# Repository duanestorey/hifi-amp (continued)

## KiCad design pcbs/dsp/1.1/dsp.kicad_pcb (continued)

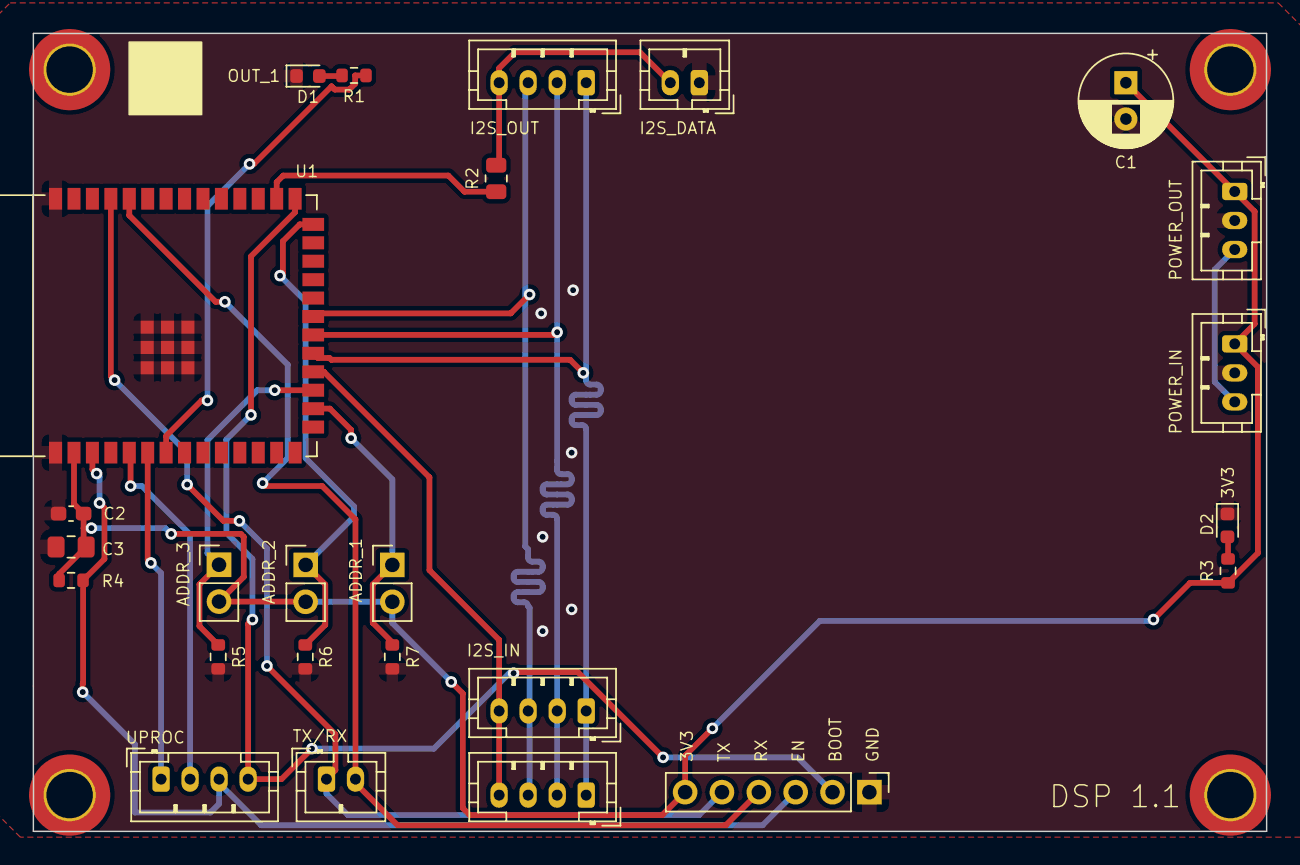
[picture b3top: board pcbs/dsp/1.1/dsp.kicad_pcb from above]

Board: 2 copper layers, 85.0 x 55.0 mm, 29 parts (0 on the bottom side), 21 nets.

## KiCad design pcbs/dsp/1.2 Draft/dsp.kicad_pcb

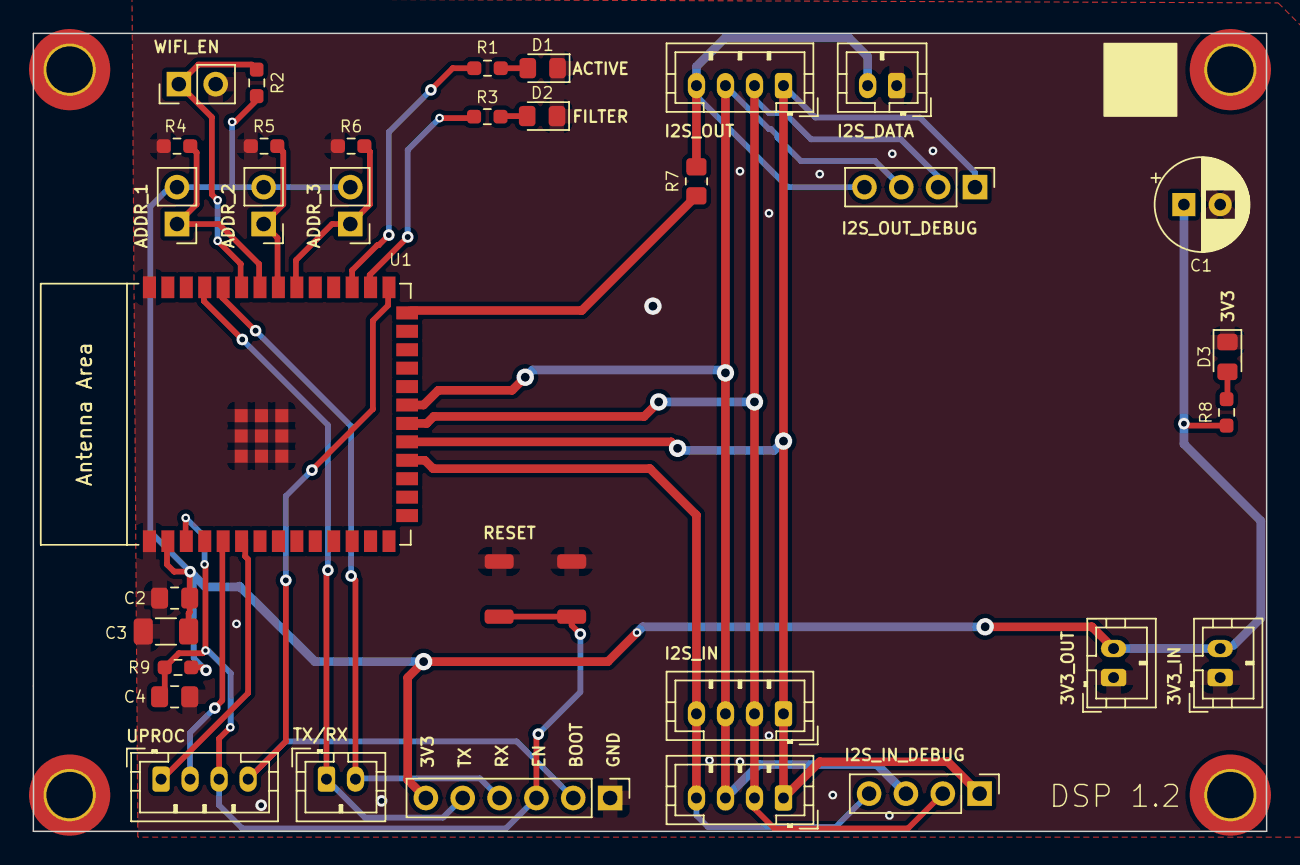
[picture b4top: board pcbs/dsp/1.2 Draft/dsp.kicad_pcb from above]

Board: 2 copper layers, 85.0 x 55.0 mm, 37 parts (0 on the bottom side), 23 nets.

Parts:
C1: 220u 16V; CP_Radial_D6.3mm_P2.50mm
C2, C4: 0.1u; C_0805_2012Metric_Pad1.18x1.45mm_HandSolder
C3: 10u; C_1206_3216Metric_Pad1.33x1.80mm_HandSolder
D1: RED; D_0805_2012Metric_Pad1.15x1.40mm_HandSolder
D2, D3: BLUE; D_0805_2012Metric_Pad1.15x1.40mm_HandSolder
H1, H2, H3, H4: MountingHole; MountingHole_3.2mm_M3_DIN965_Pad_TopOnly
J1, J5, J6, J7: Conn_01x02_Pin; PinHeader_1x02_P2.54mm_Vertical
J2, J10, J11, J15: Conn_01x04_Pin; JST_PH_B4B-PH-K_1x04_P2.00mm_Vertical
J3, J8, J9, J12: Conn_01x02_Pin; JST_PH_B2B-PH-K_1x02_P2.00mm_Vertical
J4, J13: Conn_01x04_Pin; PinHeader_1x04_P2.54mm_Vertical
J14: Conn_01x06_Pin; PinHeader_1x06_P2.54mm_Vertical
R1, R3, R8: 150R; R_0603_1608Metric_Pad0.98x0.95mm_HandSolder
R2, R4, R5, R6, R9: 4.7K; R_0603_1608Metric_Pad0.98x0.95mm_HandSolder
R7: 22R; R_0805_2012Metric_Pad1.20x1.40mm_HandSolder
SW1: SW_Push; Button Aliexpress 4x4
U1: ESP32-S3-WROOM-1

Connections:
3V3: C1.1, C2.1, C3.1, J5.2, J6.2, J7.2, J8.2, J9.2, J14.6, R2.2, R8.1, R9.1, U1.2 (3V3)
ACTIVE: R1.1, U1.29 (SPIIO7/GPIO36/FSPICLK/SUBSPICLK)
ADDR1: J5.1, R4.1, U1.34 (MTDI/GPIO41/CLK_OUT1)
ADDR2: J6.1, R5.1, U1.33 (MTDO/GPIO40/CLK_OUT2)
ADDR3: J7.1, R6.1, U1.32 (MTCK/GPIO39/CLK_OUT3/SUBSPICS1)
BOOT: J11.4, J14.2, U1.27 (GPIO0/BOOT)
EN: C4.1, J11.3, J14.3, R9.2, SW1.1, U1.3 (EN)
FILTER: R3.1, U1.28 (SPIIO6/GPIO35/FSPID/SUBSPID)
GND: C1.2, C2.2, C3.2, C4.2, D1.1 (K), D2.1 (K), D3.1 (K), J1.2, J3.1, J8.1, J9.1, J14.1, R4.2, R5.2, R6.2, SW1.2, U1.1 (GND), U1.40 (GND), U1.41 (GND)
I2S_IN_BCLK: J2.2, J4.2, J10.2, J13.2, J15.2, U1.20 (GPIO12/TOUCH12/ADC2_CH1/FSPICLK/FSPIIO6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)
I2S_IN_DATA: J10.4, J13.4, J15.4, U1.18 (GPIO10/TOUCH10/ADC1_CH9/FSPICS0/FSPIIO4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)
I2S_IN_LRCLK: J2.3, J4.3, J10.3, J13.3, J15.3, U1.21 (GPIO13/TOUCH13/ADC2_CH2/FSPIQ/FSPIIO7/S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)
I2S_IN_MCLK: J2.1, J4.1, J10.1, J13.1, J15.1, U1.19 (GPIO11/TOUCH11/ADC2_CH0/FSPID/FSPIIO5/S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)
I2S_OUT_DATA: J2.4, J3.2, J4.4, R7.2
unnamed: D1.2 (A), R1.2
unnamed: D2.2 (A), R3.2
unnamed: D3.2 (A), R8.2
unnamed: R7.1, U1.26 (GPIO45)
RX: J12.2, J14.4, U1.36 (U0RXD/GPIO44/CLK_OUT2)
SCL: J11.1, U1.6 (GPIO6/TOUCH6/ADC1_CH5)
SDA: J11.2, U1.5 (GPIO5/TOUCH5/ADC1_CH4)
TX: J12.1, J14.5, U1.37 (U0TXD/GPIO43/CLK_OUT1)
WIFI_EN: J1.1, R2.1, U1.35 (MTMS/GPIO42)

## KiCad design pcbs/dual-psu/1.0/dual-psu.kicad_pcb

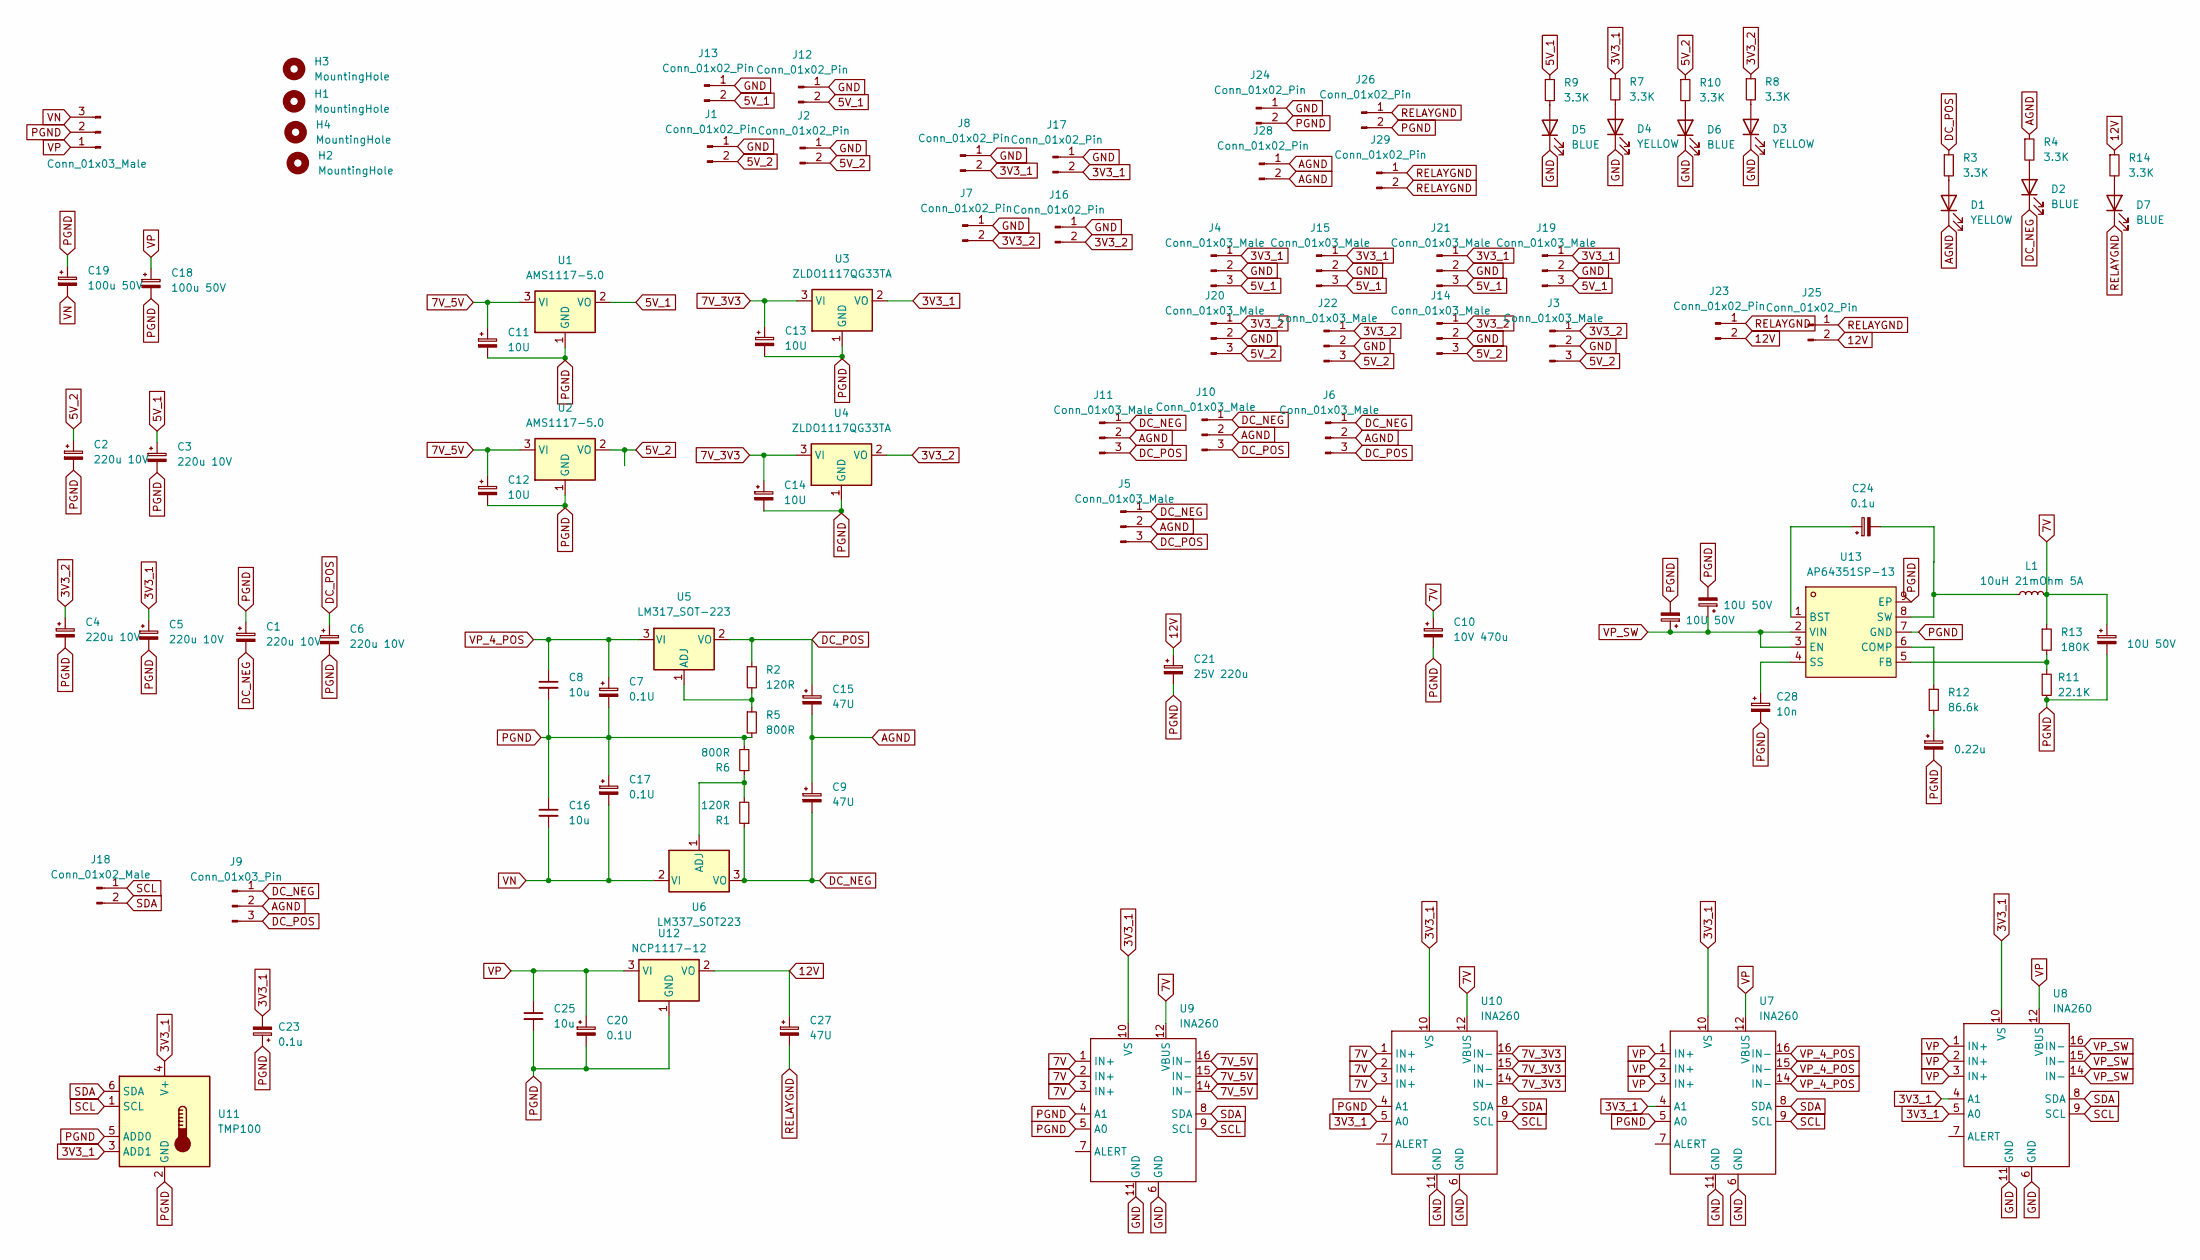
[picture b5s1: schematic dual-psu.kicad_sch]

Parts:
C1, C2, C3, C4, C5, C6: 220u 10V; CP_Radial_D6.3mm_P2.50mm
C7, C17, C20: 0.1U; C_0603_1608Metric_Pad1.08x0.95mm_HandSolder
C8, C16, C25: 10u; C_1206_3216Metric_Pad1.33x1.80mm_HandSolder
C9, C15, C27: 47U; C_1206_3216Metric_Pad1.33x1.80mm_HandSolder
C10: 10V 470u; CP_Radial_D8.0mm_P3.50mm
C11, C12, C13, C14: 10U; C_1206_3216Metric_Pad1.33x1.80mm_HandSolder
C18, C19: 100u 50V; CP_Radial_D8.0mm_P3.50mm
C21: 25V 220u; CP_Radial_D8.0mm_P3.50mm
C22, C29, C30: 10U 50V; C_1206_3216Metric_Pad1.33x1.80mm_HandSolder
C23, C24: 0.1u; C_0805_2012Metric_Pad1.18x1.45mm_HandSolder
C26: 0.22u; C_0805_2012Metric_Pad1.18x1.45mm_HandSolder
C28: 10n; C_0805_2012Metric_Pad1.18x1.45mm_HandSolder
D1: YELLOW; LED_0603_1608Metric
D2, D7: BLUE; LED_0603_1608Metric
D3, D4: YELLOW; LED_0805_2012Metric_Pad1.15x1.40mm_HandSolder
D5, D6: BLUE; LED_0805_2012Metric_Pad1.15x1.40mm_HandSolder
H1, H2, H3, H4: MountingHole; MountingHole_3.2mm_M3_DIN965_Pad_TopOnly
J1, J2, J7, J8, J12, J13, J16, J17, J23, J25, J28, J29: Conn_01x02_Pin; JST_PH_B2B-PH-K_1x02_P2.00mm_Vertical
J3, J4, J5, J6, J10, J11, J14, J15, J19, J20, J21, J22: Conn_01x03_Male; JST_PH_B3B-PH-K_1x03_P2.00mm_Vertical
J9: Conn_01x03_Pin; PinHeader_1x03_P2.54mm_Vertical
J18: Conn_01x02_Male; JST_PH_B2B-PH-K_1x02_P2.00mm_Vertical
J24, J26: Conn_01x02_Pin; PinHeader_1x02_P2.54mm_Vertical
J27: Conn_01x03_Male; JST_VH_B3P-VH_1x03_P3.96mm_Vertical
L1: 10uH 21mOhm 5A; L_Vishay_IHLP-4040; Mouser 704-DR1040-7R0-R
R1, R2: 120R; R_0603_1608Metric_Pad0.98x0.95mm_HandSolder
R3, R4, R7, R8, R9, R10, R14: 3.3K; R_0603_1608Metric_Pad0.98x0.95mm_HandSolder
R5, R6: 800R; R_0603_1608Metric_Pad0.98x0.95mm_HandSolder
R11: 22.1K; R_0603_1608Metric_Pad0.98x0.95mm_HandSolder; Mouser 603-RC0603JR-07820KP
R12: 86.6k; R_0603_1608Metric_Pad0.98x0.95mm_HandSolder; Mouser 71-CRCW0603-86.6K-E3
R13: 180K; R_0603_1608Metric_Pad0.98x0.95mm_HandSolder; Mouser 603-RC0603JR-10180KL
U1, U2: AMS1117-5.0; SOT-223-3_TabPin2; Mouser 926-LM1117MPX5.0NOPB
U3, U4: ZLDO1117QG33TA; SOT-223-3_TabPin2; Mouser ZLDO1117QG33TA
U5: LM317_SOT-223; SOT-223-3_TabPin2; Mouser 595-LM317DCY
U6: LM337_SOT223; SOT-223-3_TabPin2; Mouser 926-LM337IMPX/NOPB
U7, U8, U9, U10: INA260; TSSOP-16_4.4x5mm_P0.65mm
U11: TMP100; SOT-23-6; Mouser 595-TMP100NA/3K
U12: NCP1117-12; SOT-223; Mouser 863-NCP1117ST12T3G
U13: AP64351SP-13; SOIC-8_L4.9-W3.9-P1.27-LS6.0-BL-EP; LCSC Part C3192339

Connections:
3V3_1: C5.1, C23.2, J4.1, J8.2, J15.1, J17.2, J19.1, J21.1, R7.1, U3.2 (VO), U7.4 (A1), U7.10 (VS), U8.4 (A1), U8.5 (A0), U8.10 (VS), U9.10 (VS), U10.5 (A0), U10.10 (VS), U11.3 (ADD1), U11.4 (V+)
3V3_2: C4.1, J3.1, J7.2, J14.1, J16.2, J20.1, J22.1, R8.1, U4.2 (VO)
5V_1: C3.1, J4.3, J12.2, J13.2, J15.3, J19.3, J21.3, R9.1, U1.2 (VO)
5V_2: C2.1, J1.2, J2.2, J3.3, J14.3, J20.3, J22.3, R10.1, U2.2 (VO)
7V: C10.1, C22.1, L1.2, R13.1, U9.1 (IN+), U9.2 (IN+), U9.3 (IN+), U9.12 (VBUS), U10.1 (IN+), U10.2 (IN+), U10.3 (IN+), U10.12 (VBUS)
7V_3V3: C13.1, C14.1, U3.3 (VI), U4.3 (VI), U10.14 (IN-), U10.15 (IN-), U10.16 (IN-)
7V_5V: C11.1, C12.1, U1.3 (VI), U2.3 (VI), U9.14 (IN-), U9.15 (IN-), U9.16 (IN-)
12V: C21.1, C27.1, J23.2, J25.2, R14.1, U12.2 (VO)
AGND: C9.1, C15.2, D1.1 (K), J5.2, J6.2, J9.2, J10.2, J11.2, J28.1, J28.2, R4.1
DC_NEG: C1.2, C9.2, D2.1 (K), J5.1, J6.1, J9.1, J10.1, J11.1, R1.1, U6.3 (VO)
DC_POS: C6.1, C15.1, J5.3, J6.3, J9.3, J10.3, J11.3, R2.1, R3.1, U5.2 (VO)
GND: D3.1 (K), D4.1 (K), D5.1 (K), D6.1 (K), J1.1, J2.1, J3.2, J4.2, J7.1, J8.1, J12.1, J13.1, J14.2, J15.2, J16.1, J17.1, J19.2, J20.2, J21.2, J22.2, J24.1, U7.6 (GND), U7.11 (GND), U8.6 (GND), U8.11 (GND), U9.6 (GND), U9.11 (GND), U10.6 (GND), U10.11 (GND)
unnamed: C26.1, R12.2
unnamed: D1.2 (A), R3.2
unnamed: D2.2 (A), R4.2
unnamed: D3.2 (A), R8.2
unnamed: D4.2 (A), R7.2
unnamed: D5.2 (A), R9.2
unnamed: D6.2 (A), R10.2
unnamed: D7.2 (A), R14.2
unnamed: R2.2, R5.1, U5.1 (ADJ)
unnamed: R1.2, R6.1, U6.1 (ADJ)
unnamed: C24.1, U13.1 (BST)
unnamed: R12.1, U13.6 (COMP)
unnamed: R11.1, R13.2, U13.5 (FB)
unnamed: C28.1, U13.4 (SS)
unnamed: C24.2, L1.1, U13.8 (SW)
PGND: C1.1, C2.2, C3.2, C4.2, C5.2, C6.2, C7.2, C8.2, C10.2, C11.2, C12.2, C13.2, C14.2, C16.1, C17.1, C18.2, C19.1, C20.2, C21.2, C22.2, C23.1, C25.2, C26.2, C28.2, C29.2, C30.2, J24.2, J26.2, J27.2, R5.2, R6.2, R11.2, U1.1 (GND), U2.1 (GND), U3.1 (GND), U4.1 (GND), U7.5 (A0), U9.4 (A1), U9.5 (A0), U10.4 (A1), U11.2 (GND), U11.5 (ADD0), U12.1 (GND), U13.7 (GND), U13.9 (EP)
RELAYGND: C27.2, D7.1 (K), J23.1, J25.1, J26.1, J29.1, J29.2
SCL: J18.1, U7.9 (SCL), U8.9 (SCL), U9.9 (SCL), U10.9 (SCL), U11.1 (SCL)
SDA: J18.2, U7.8 (SDA), U8.8 (SDA), U9.8 (SDA), U10.8 (SDA), U11.6 (SDA)
VN: C16.2, C17.2, C19.2, J27.3, U6.2 (VI)
VP: C18.1, C20.1, C25.1, J27.1, U7.1 (IN+), U7.2 (IN+), U7.3 (IN+), U7.12 (VBUS), U8.1 (IN+), U8.2 (IN+), U8.3 (IN+), U8.12 (VBUS), U12.3 (VI)
VP_4_POS: C7.1, C8.1, U5.3 (VI), U7.14 (IN-), U7.15 (IN-), U7.16 (IN-)
VP_SW: C29.1, C30.1, U8.14 (IN-), U8.15 (IN-), U8.16 (IN-), U13.2 (VIN), U13.3 (EN)

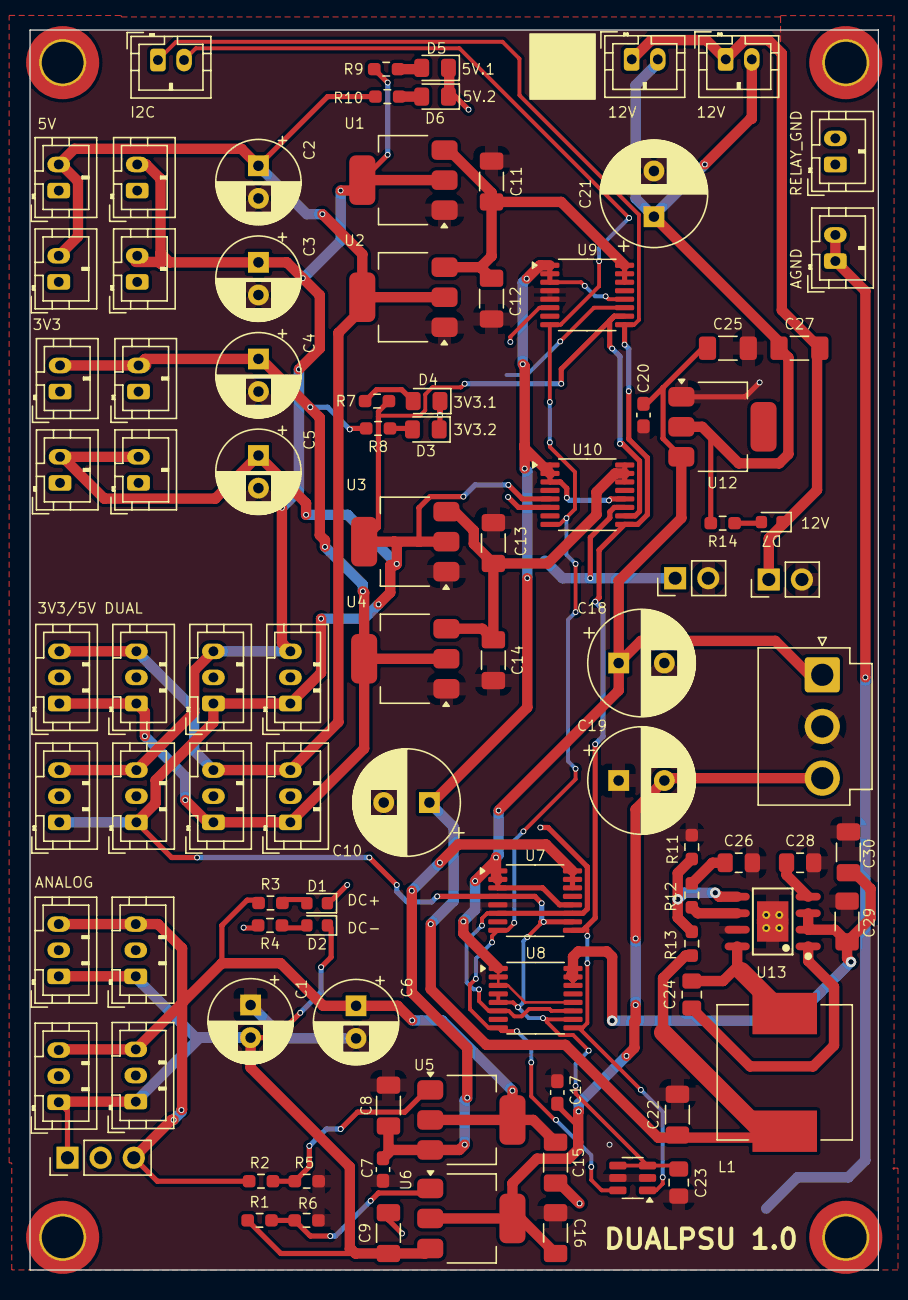
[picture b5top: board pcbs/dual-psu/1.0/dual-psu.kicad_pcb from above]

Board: 2 copper layers, 65.0 x 95.0 mm, 98 parts (0 on the bottom side), 35 nets.

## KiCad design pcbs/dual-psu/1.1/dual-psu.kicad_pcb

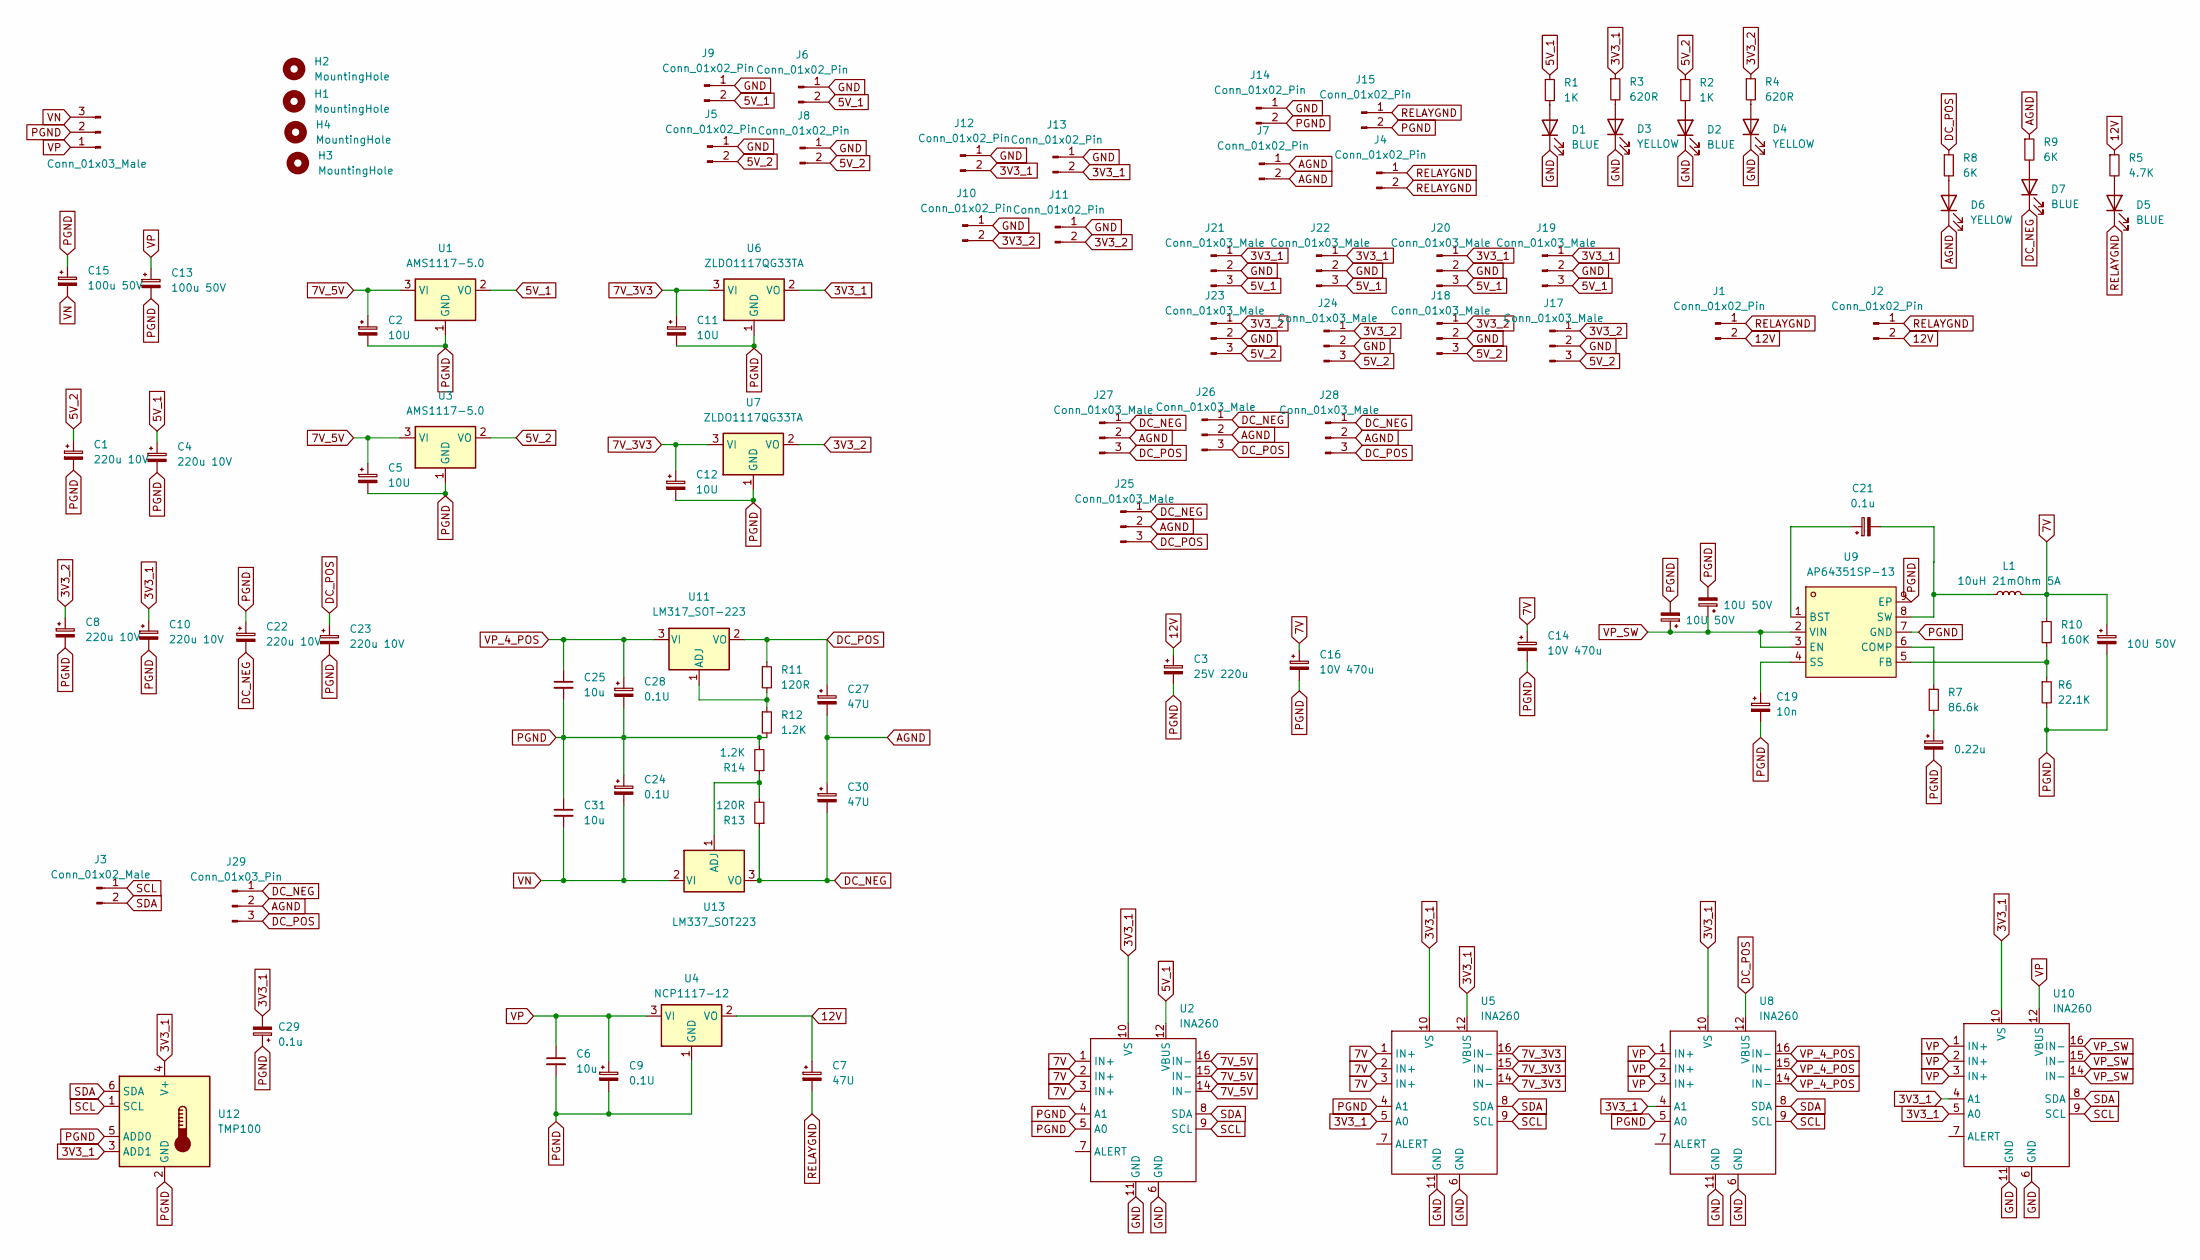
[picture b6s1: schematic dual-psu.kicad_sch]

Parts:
C1, C4, C8, C10, C22, C23: 220u 10V; CP_Radial_D6.3mm_P2.50mm
C2, C5, C11, C12: 10U; C_1206_3216Metric_Pad1.33x1.80mm_HandSolder
C3: 25V 220u; CP_Radial_D8.0mm_P3.50mm
C6, C25, C31: 10u; C_1206_3216Metric_Pad1.33x1.80mm_HandSolder
C7, C27, C30: 47U; C_1206_3216Metric_Pad1.33x1.80mm_HandSolder
C9, C24, C28: 0.1U; C_0603_1608Metric_Pad1.08x0.95mm_HandSolder
C13, C15: 100u 50V; CP_Radial_D8.0mm_P3.50mm
C14, C16: 10V 470u; CP_Radial_D8.0mm_P3.50mm
C17, C20, C26: 10U 50V; C_1206_3216Metric_Pad1.33x1.80mm_HandSolder
C18: 0.22u; C_0805_2012Metric_Pad1.18x1.45mm_HandSolder
C19: 10n; C_0805_2012Metric_Pad1.18x1.45mm_HandSolder
C21, C29: 0.1u; C_0805_2012Metric_Pad1.18x1.45mm_HandSolder
D1, D2, D5, D7: BLUE; LED_0603_1608Metric_Pad1.05x0.95mm_HandSolder
D3, D4, D6: YELLOW; LED_0603_1608Metric_Pad1.05x0.95mm_HandSolder
H1, H2, H3, H4: MountingHole; MountingHole_3.2mm_M3_DIN965_Pad_TopOnly
J1, J2, J4, J5, J6, J7, J8, J9, J10, J11, J12, J13: Conn_01x02_Pin; JST_PH_B2B-PH-K_1x02_P2.00mm_Vertical
J3: Conn_01x02_Male; JST_PH_B2B-PH-K_1x02_P2.00mm_Vertical
J14, J15: Conn_01x02_Pin; PinHeader_1x02_P2.54mm_Vertical
J16: Conn_01x03_Male; JST_VH_B3P-VH_1x03_P3.96mm_Vertical
J17, J18, J19, J20, J21, J22, J23, J24, J25, J26, J27, J28: Conn_01x03_Male; JST_PH_B3B-PH-K_1x03_P2.00mm_Vertical
J29: Conn_01x03_Pin; PinHeader_1x03_P2.54mm_Vertical
L1: 10uH 21mOhm 5A; L_Vishay_IHLP-4040; Mouser 704-DR1040-7R0-R
R1, R2: 1K; R_0603_1608Metric_Pad0.98x0.95mm_HandSolder
R3, R4: 620R; R_0603_1608Metric_Pad0.98x0.95mm_HandSolder
R5: 4.7K; R_0603_1608Metric_Pad0.98x0.95mm_HandSolder
R6: 22.1K; R_0603_1608Metric_Pad0.98x0.95mm_HandSolder; Mouser 603-RC0603JR-07820KP
R7: 86.6k; R_0603_1608Metric_Pad0.98x0.95mm_HandSolder; Mouser 71-CRCW0603-86.6K-E3
R8, R9: 6K; R_0603_1608Metric_Pad0.98x0.95mm_HandSolder
R10: 160K; R_0603_1608Metric_Pad0.98x0.95mm_HandSolder; Mouser 603-RC0603JR-10180KL
R11, R13: 120R; R_0603_1608Metric_Pad0.98x0.95mm_HandSolder
R12, R14: 1.2K; R_0603_1608Metric_Pad0.98x0.95mm_HandSolder
U1, U3: AMS1117-5.0; SOT-223-3_TabPin2; Mouser 926-LM1117MPX5.0NOPB
U2, U5, U8, U10: INA260; TSSOP-16_4.4x5mm_P0.65mm
U4: NCP1117-12; SOT-223; Mouser 863-NCP1117ST12T3G
U6, U7: ZLDO1117QG33TA; SOT-223-3_TabPin2; Mouser ZLDO1117QG33TA
U9: AP64351SP-13; SOIC-8_L4.9-W3.9-P1.27-LS6.0-BL-EP; LCSC Part C3192339
U11: LM317_SOT-223; SOT-223-3_TabPin2; Mouser 595-LM317DCY
U12: TMP100; SOT-23-6; Mouser 595-TMP100NA/3K
U13: LM337_SOT223; SOT-223-3_TabPin2; Mouser 926-LM337IMPX/NOPB

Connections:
3V3_1: C10.1, C29.2, J12.2, J13.2, J19.1, J20.1, J21.1, J22.1, R3.1, U2.10 (VS), U5.5 (A0), U5.10 (VS), U5.12 (VBUS), U6.2 (VO), U8.4 (A1), U8.10 (VS), U10.4 (A1), U10.5 (A0), U10.10 (VS), U12.3 (ADD1), U12.4 (V+)
3V3_2: C8.1, J10.2, J11.2, J17.1, J18.1, J23.1, J24.1, R4.1, U7.2 (VO)
5V_1: C4.1, J6.2, J9.2, J19.3, J20.3, J21.3, J22.3, R1.1, U1.2 (VO), U2.12 (VBUS)
5V_2: C1.1, J5.2, J8.2, J17.3, J18.3, J23.3, J24.3, R2.1, U3.2 (VO)
7V: C14.1, C16.1, C26.1, L1.2, R10.1, U2.1 (IN+), U2.2 (IN+), U2.3 (IN+), U5.1 (IN+), U5.2 (IN+), U5.3 (IN+)
7V_3V3: C11.1, C12.1, U5.14 (IN-), U5.15 (IN-), U5.16 (IN-), U6.3 (VI), U7.3 (VI)
7V_5V: C2.1, C5.1, U1.3 (VI), U2.14 (IN-), U2.15 (IN-), U2.16 (IN-), U3.3 (VI)
12V: C3.1, C7.1, J1.2, J2.2, R5.1, U4.2 (VO)
AGND: C27.2, C30.1, D6.1 (K), J7.1, J7.2, J25.2, J26.2, J27.2, J28.2, J29.2, R9.1
DC_NEG: C22.2, C30.2, D7.1 (K), J25.1, J26.1, J27.1, J28.1, J29.1, R13.1, U13.3 (VO)
DC_POS: C23.1, C27.1, J25.3, J26.3, J27.3, J28.3, J29.3, R8.1, R11.1, U8.12 (VBUS), U11.2 (VO)
GND: D1.1 (K), D2.1 (K), D3.1 (K), D4.1 (K), J5.1, J6.1, J8.1, J9.1, J10.1, J11.1, J12.1, J13.1, J14.1, J17.2, J18.2, J19.2, J20.2, J21.2, J22.2, J23.2, J24.2, U2.6 (GND), U2.11 (GND), U5.6 (GND), U5.11 (GND), U8.6 (GND), U8.11 (GND), U10.6 (GND), U10.11 (GND)
unnamed: C18.1, R7.2
unnamed: D1.2 (A), R1.2
unnamed: D2.2 (A), R2.2
unnamed: D3.2 (A), R3.2
unnamed: D4.2 (A), R4.2
unnamed: D5.2 (A), R5.2
unnamed: D6.2 (A), R8.2
unnamed: D7.2 (A), R9.2
unnamed: C21.1, U9.1 (BST)
unnamed: R7.1, U9.6 (COMP)
unnamed: R6.1, R10.2, U9.5 (FB)
unnamed: C19.1, U9.4 (SS)
unnamed: C21.2, L1.1, U9.8 (SW)
unnamed: R11.2, R12.1, U11.1 (ADJ)
unnamed: R13.2, R14.1, U13.1 (ADJ)
PGND: C1.2, C2.2, C3.2, C4.2, C5.2, C6.2, C8.2, C9.2, C10.2, C11.2, C12.2, C13.2, C14.2, C15.1, C16.2, C17.2, C18.2, C19.2, C20.2, C22.1, C23.2, C24.1, C25.2, C26.2, C28.2, C29.1, C31.1, J14.2, J15.2, J16.2, R6.2, R12.2, R14.2, U1.1 (GND), U2.4 (A1), U2.5 (A0), U3.1 (GND), U4.1 (GND), U5.4 (A1), U6.1 (GND), U7.1 (GND), U8.5 (A0), U9.7 (GND), U9.9 (EP), U12.2 (GND), U12.5 (ADD0)
RELAYGND: C7.2, D5.1 (K), J1.1, J2.1, J4.1, J4.2, J15.1
SCL: J3.1, U2.9 (SCL), U5.9 (SCL), U8.9 (SCL), U10.9 (SCL), U12.1 (SCL)
SDA: J3.2, U2.8 (SDA), U5.8 (SDA), U8.8 (SDA), U10.8 (SDA), U12.6 (SDA)
VN: C15.2, C24.2, C31.2, J16.3, U13.2 (VI)
VP: C6.1, C9.1, C13.1, J16.1, U4.3 (VI), U8.1 (IN+), U8.2 (IN+), U8.3 (IN+), U10.1 (IN+), U10.2 (IN+), U10.3 (IN+), U10.12 (VBUS)
VP_4_POS: C25.1, C28.1, U8.14 (IN-), U8.15 (IN-), U8.16 (IN-), U11.3 (VI)
VP_SW: C17.1, C20.1, U9.2 (VIN), U9.3 (EN), U10.14 (IN-), U10.15 (IN-), U10.16 (IN-)

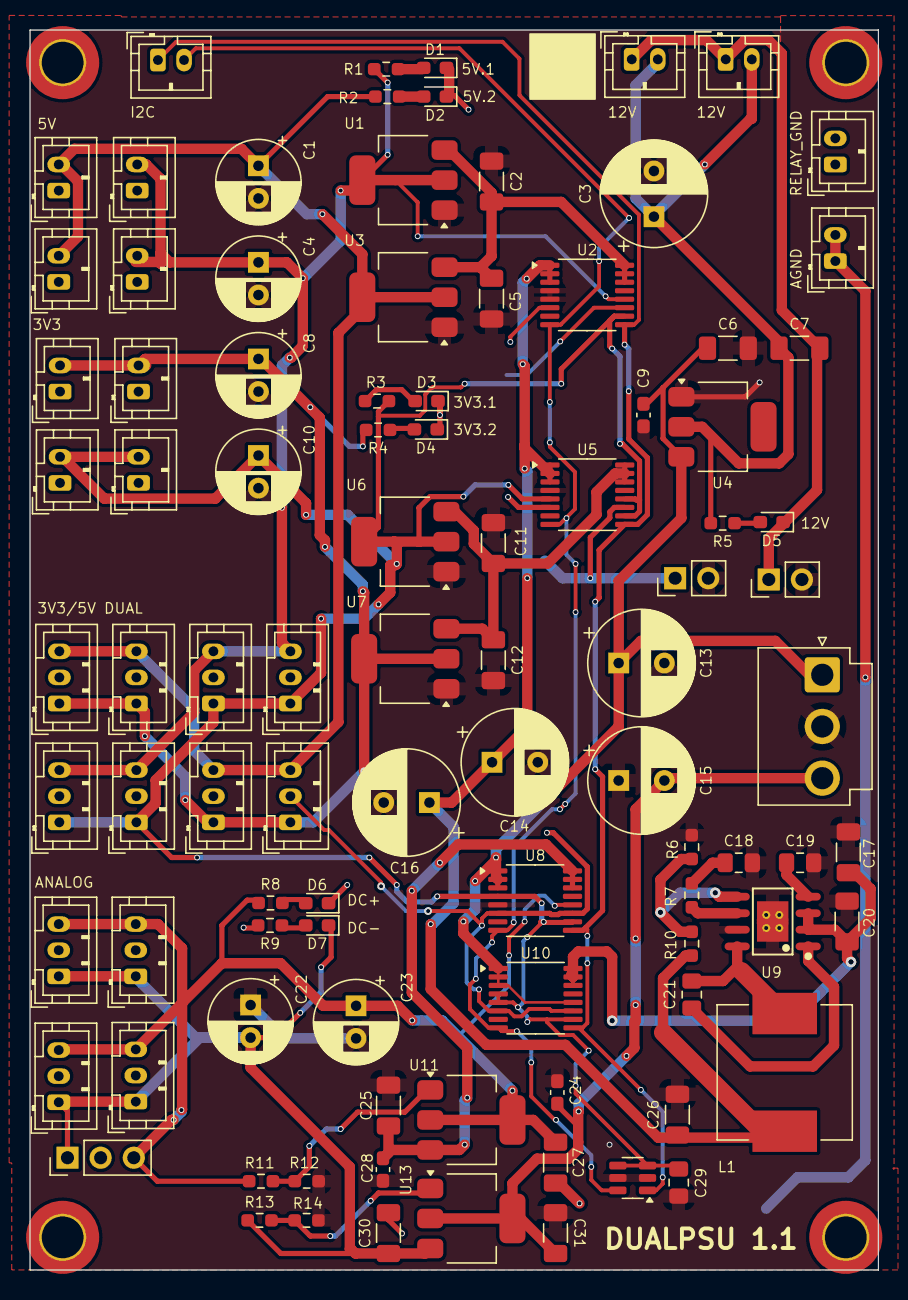
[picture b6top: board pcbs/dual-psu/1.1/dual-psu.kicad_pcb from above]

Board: 2 copper layers, 65.0 x 95.0 mm, 99 parts (0 on the bottom side), 35 nets.
